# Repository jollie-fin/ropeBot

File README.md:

ropeBot
=======

The aim is to develop a computer game and a robot, with interactions between both. The idea is to have a new experience

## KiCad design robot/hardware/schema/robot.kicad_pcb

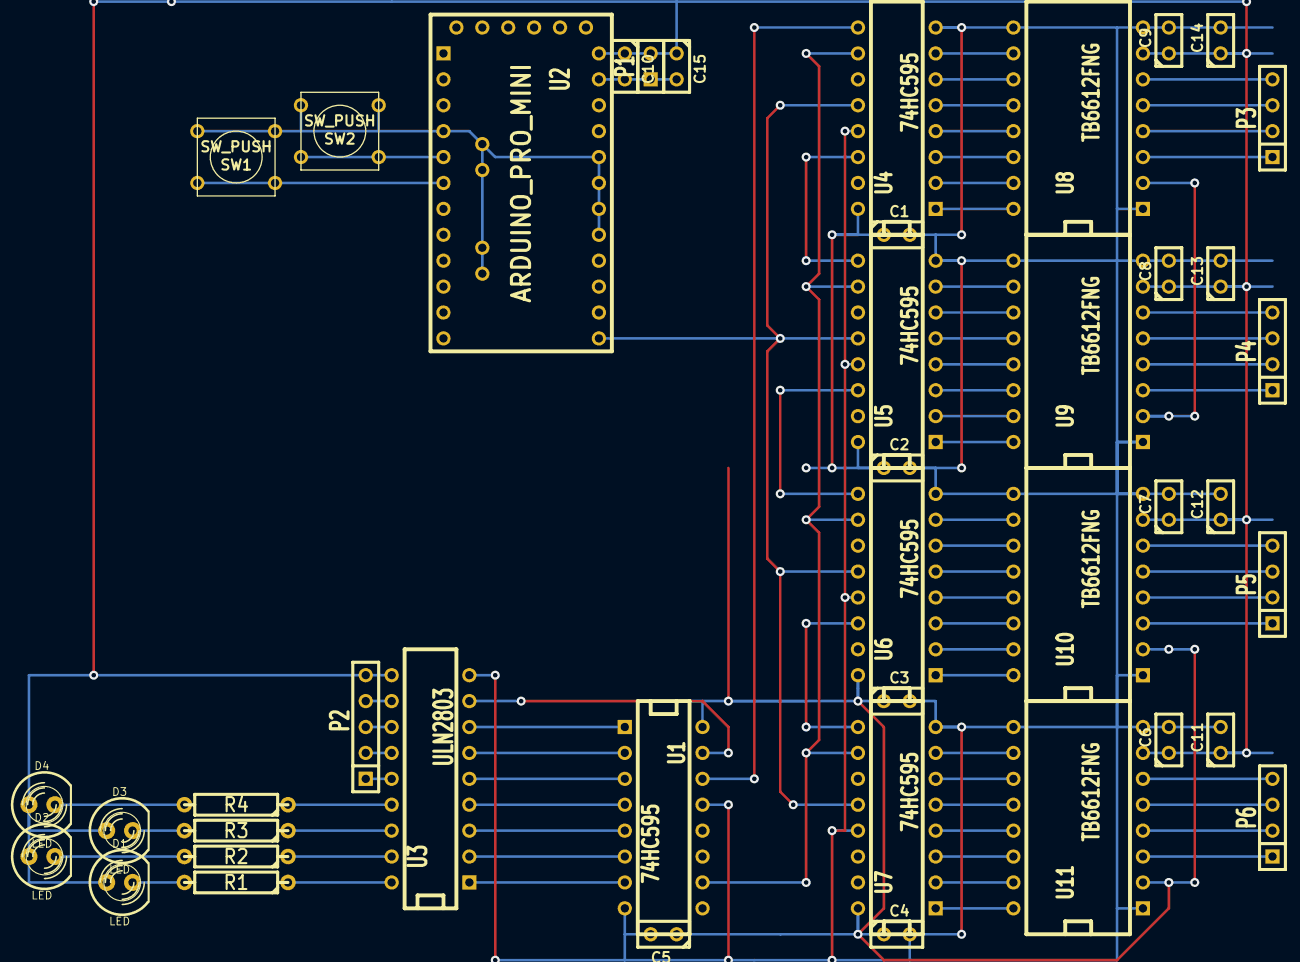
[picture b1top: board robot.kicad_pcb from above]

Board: 2 copper layers, 42 parts (0 on the bottom side), 77 nets.

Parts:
C1, C2, C3, C4, C5, C6, C7, C8, C9, C10: C; C1
C11, C12, C13, C14, C15: CP; C1
D1, D2, D3, D4: LED; LED-5MM
P1: CONN_2; SIL-2
P2: CONN_5; SIL-5
P3, P4, P5, P6: CONN_4; SIL-4
R1, R2, R3, R4: R; R4
SW1, SW2: SW_PUSH; SW_PUSH_SMALL
U1, U4, U5, U6, U7: 74HC595; DIP-16__300
U2: ARDUINO_PRO_MINI; ArduinoProMini
U3: ULN2803; DIP-18__300
U8, U9, U10, U11: TB6612FNG; DIP-16__500

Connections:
GND: C1.2, C2.2, C3.2, C4.2, C5.2, C6.2, C7.2, C8.2, C9.2, C10.2, C11.2, C12.2, C13.2, C14.2, C15.2, P1.1, SW1.2, SW2.2, U1.8, U1.13, U2.1C, U2.1D, U2.2A, U2.2C, U2.2D, U2.5A, U2.6A, U2.7A, U2.8A, U2.9B, U3.9, U4.8, U4.13, U5.8, U5.13, U6.8, U6.13, U7.8, U7.13, U8.1, U8.8, U8.9, U9.1, U9.8, U9.9, U10.1, U10.8, U10.9, U11.1, U11.8, U11.9
unnamed: U6.6, U10.11
unnamed: U6.5, U10.12
unnamed: U6.4, U10.13
unnamed: U6.3, U10.14
unnamed: U6.2, U10.15
unnamed: U6.7, U10.10
unnamed: U6.1, U10.16
unnamed: P2.1, U3.14
unnamed: P2.2, U3.13
unnamed: P2.3, U3.12
unnamed: P2.4, U3.11
unnamed: P4.1, U9.3
unnamed: U5.7, U9.10
unnamed: U5.6, U9.11
unnamed: U5.5, U9.12
unnamed: U5.4, U9.13
unnamed: U5.3, U9.14
unnamed: U5.2, U9.15
unnamed: U5.1, U9.16
unnamed: P5.2, U10.4
unnamed: P5.1, U10.3
unnamed: U1.5, U3.3
unnamed: U1.4, U3.4
unnamed: U1.3, U3.5
unnamed: U1.2, U3.6
unnamed: R1.1, U3.18
unnamed: R4.1, U3.15
unnamed: R3.1, U3.16
unnamed: R2.1, U3.17
unnamed: P4.2, U9.4
unnamed: U1.7, U3.1
unnamed: U1.6, U3.2
unnamed: D1.2, R1.2
unnamed: D2.2, R2.2
unnamed: D3.2, R3.2
unnamed: D4.2, R4.2
unnamed: SW1.1, U2.7B
unnamed: SW2.1, U2.8B
unnamed: U4.7, U8.10
unnamed: U7.2, U11.15
unnamed: U7.7, U11.10
unnamed: U7.6, U11.11
unnamed: U7.5, U11.12
unnamed: U7.4, U11.13
unnamed: U7.3, U11.14
unnamed: P6.1, U11.3
unnamed: U7.1, U11.16
unnamed: U4.2, U8.15
unnamed: U4.6, U8.11
unnamed: U4.5, U8.12
unnamed: U4.4, U8.13
unnamed: U4.3, U8.14
unnamed: U4.1, U8.16
unnamed: P6.2, U11.4
unnamed: U5.14, U6.9
unnamed: U4.14, U5.9
unnamed: U1.14, U4.9
unnamed: U2.11A, U7.14
unnamed: U6.14, U7.9
unnamed: U1.1, U3.7
unnamed: U1.15, U3.8
unnamed: U1.12, U2.12A, U4.12, U5.12, U6.12, U7.12
unnamed: P5.3, U10.5
unnamed: P4.3, U9.5
unnamed: P3.3, U8.5
unnamed: P5.4, U10.6
unnamed: P3.4, U8.6
unnamed: P4.4, U9.6
unnamed: P6.4, U11.6
unnamed: P6.3, U11.5
unnamed: U1.10, U2.1B, U4.10, U5.10, U6.10, U7.10
unnamed: U1.11, U2.9A, U4.11, U5.11, U6.11, U7.11
unnamed: P3.1, U8.3
unnamed: P3.2, U8.4
VCC: C1.1, C2.1, C3.1, C4.1, C5.1, U1.16, U2.4A, U4.16, U5.16, U6.16, U7.16, U8.2, U9.2, U10.2, U11.2
VMOT: C6.1, C7.1, C8.1, C9.1, C10.1, C11.1, C12.1, C13.1, C14.1, C15.1, D1.1, D2.1, D3.1, D4.1, P1.2, P2.5, U2.1A, U3.10, U8.7, U9.7, U10.7, U11.7

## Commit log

2014-03-25 Création du fichier d'index.
2014-03-25 Rajout d'un fichier vide représentant le code du robot
2014-03-25 Fichier inutile avec une idee de titre stupide
2014-03-26 Un dossier pour mettre des idees
2014-03-26 Adding a first draft of the board
2014-03-26 Moving the board to the Idee folder
2014-03-26 Déplacement du fichier grille_paf.svg dans le répertoire Idees.
2014-03-26 Changes in the board and level file
2014-03-27 Changes to board and levels files
2014-04-02 Création d'un fichier d'expérimentation de svg
2014-04-02 Changement d'extension pour xml.
2014-04-02 La première case !
2014-04-02 La génération du plateau fonctionne \o/
2014-04-02 Smiley!
2014-04-02 Ajout des symboles. Couleurs définies dans une table associative.
2014-04-02 Ajout des triangles, carré, étoiles
2014-04-02 Transposition des descriptions de la carte. Rajout d'une table associative pour les symboles
2014-04-02 suppression de test obsolète
2014-04-02 Changing the board described in data.js to match the one described in grillePaf.svg
2014-04-06 Design des tuiles et des legendes
2014-04-07 Plus de legendes
2014-04-12 ebauche de la gestion de la simulation
2014-04-12 Changement du titre
2014-04-12 Suppression du répertoire testapprentissage
2014-04-12 changement de l'id de nale
2014-04-12 première animation de Nale
2014-04-12 premier déplacement sans programmation
2014-04-13 Mis en œuvre d'un interpréteur de programme basique.
2014-04-13 correction d'un bug dans transformfromprogram et suppression des alerts
2014-04-13 ajout de l'indicateur 'program counter'
2014-04-13 correction du bug sur les conditions numériques
2014-04-13 correction des conditionnelles
2014-04-13 implémentation des murs et de la lave
2014-04-13 Résolution de bugs, implémentation de l'apesanteur, calcul de la trajectoire case par case
2014-04-13 L'animation est démarrée automatiquement
2014-04-13 correction du bug d'interaction entre sable et apesanteur
2014-04-13 Correction du bug de SVGOnload sous chrome
2014-04-13 Synchronisation des départs
2014-04-14 Création et utilisation de createSVGobject
2014-04-14 paramétrage de width
2014-04-14 encapsulation des données de niveaux dans des structures
2014-04-14 Modification du jeu de données
2014-04-14 implémentation de ice
2014-04-14 rajout de l'instruction N (nop)
2014-04-15 New levels file, .csv
2014-04-15 New board in grille_Paf.svg
2014-04-21 Création des fichiers du code du robot
2014-04-21 Amélioration du makefile. Création d'un fichier de définition des constantes.
2014-04-21 début d'implémentation du controleur pas-a-pas
2014-04-21 Implémentation de l'interpolation des moteurs pap. TODO : initialisation de l'interpolation
2014-04-22 Rajout d'un algorithme de calcul de racine carré rapide Commencement du calcul exacte des coordonées curvilignes des moteurs en fonction des coordonées du robot
2014-04-22 Implémentation du calcul exacte des longueurs de ficelles Il manque l'initialisation
2014-04-22 Mise en place des accesseurs pour le moteur de déplacement Correction du bug dans le linkage (Makefile)
2014-04-22 Modifications cosmétiques
2014-04-22 Rajout de l'élimination du code mort + boucle infinie à la fin du main
2014-04-22 initialisation du moteur de mouvement avec des valeurs pertinentes
2014-04-22 implémentation de l'interruption du timer0 pour le déplacement
2014-04-23 rajout du calcul des coordonnées de destination
2014-04-23 ajout de fonctionnalités de debug
2014-04-23 ajout du calcul de score
2014-04-24 Ajout de la fonction de conversion analogique numérique avec filtre anti-bruit
2014-04-24 ajout de fonction de démarrage arrêt de timer pour les moteurs pàp, pour limiter la concurrence à l'accès
2014-04-24 déclenchement de l'interruption et de l'acquisition sur timer2.
2014-04-24 rajout d'une fonction rapide d'affichage de message de debug
2014-04-24 Cosmétique
2014-04-24 Ajout de contrainte d'atomicité dans S_timestamp
2014-04-25 ajout de la détection de transitions + renforcement de l'atomicité
2014-04-25 fichier de test d'entrée
2014-04-25 implémentation du Biphase mark coding
2014-04-25 ajout générateur de forme d'onde
2014-04-25 Correction de l'inversion de sens de lecture du générateur de forme
2014-04-26 rajout d'une fonction d'affichage d'un hexadécimal
2014-04-26 Rajout de bruit dans le générateur de message
2014-04-26 Affichage de message de diagnostic des messages reçus
2014-04-28 Début de réduction de la taille des interruptions : utilisation d'un buffer + assembleur
2014-04-28 rajout d'un délai à la fin du train d'impulsions
2014-04-28 Décodage des données hors interruption
2014-04-28 correction du calcul de score
2014-06-07 Test compteur points
2014-06-07 Correction du calcul de coût d'un programme
2014-06-07 Nouvelle grille
2014-06-07 Liseré blanc autour des symboles
2014-06-07 lisere blanc
2014-06-07 liseré blanc
2014-06-07 Nouvelle grille avec les symboles en noir entoures de blanc
2014-06-08 Nouveaux niveaux
2014-06-17 Passage a des cases hexagonales
2014-06-17 La grille a la bonne taille...
2014-06-17 Dix premiers niveaux en hexagonal
2014-06-19 Passage au pavage hexagonal (déplacement de Nale non modifié)
2014-06-19 Passage en pavage hexagonal de Nalé
2014-06-19 Implémentation du déplacement de Nalé Factorisation de code
2014-06-19 encapsulation du svg dans un html
2014-06-19 Renommage de variables
2014-06-19 Ajouts de commentaires et renommage de variables
2014-06-20 Initialisation du pavage Nettoyage de data.js
2014-06-20 Manipulation de multiples niveaux
2014-06-20 inclusion de level.js
2014-08-17 Création des fichiers kicad pour le schema électrique
2014-08-17 Librairie de composants (arduino + driver moteur)
2014-08-17 Premier tirage du schéma électronique
2014-08-17 empreinte des circuits-intégrés
2014-08-17 positionnement des composants
2014-08-17 Ajout de condensateurs
2014-08-17 début de connexion. Permutation de l'ordre des registres à décalage
